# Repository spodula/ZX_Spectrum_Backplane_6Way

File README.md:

# ZX_Spectrum_Backplane_6Way
zx Spectrum backplane - 6 way

Same as the 4 way backplane except... 6 way
Also added reset button and Power LED, because why not :)
Also corrected the distances so they are all 20mm. (Seems i messed this up on the 4 way one)

Free for all use. 

Just forward the gerbers files to your favorate PCB manafactury.

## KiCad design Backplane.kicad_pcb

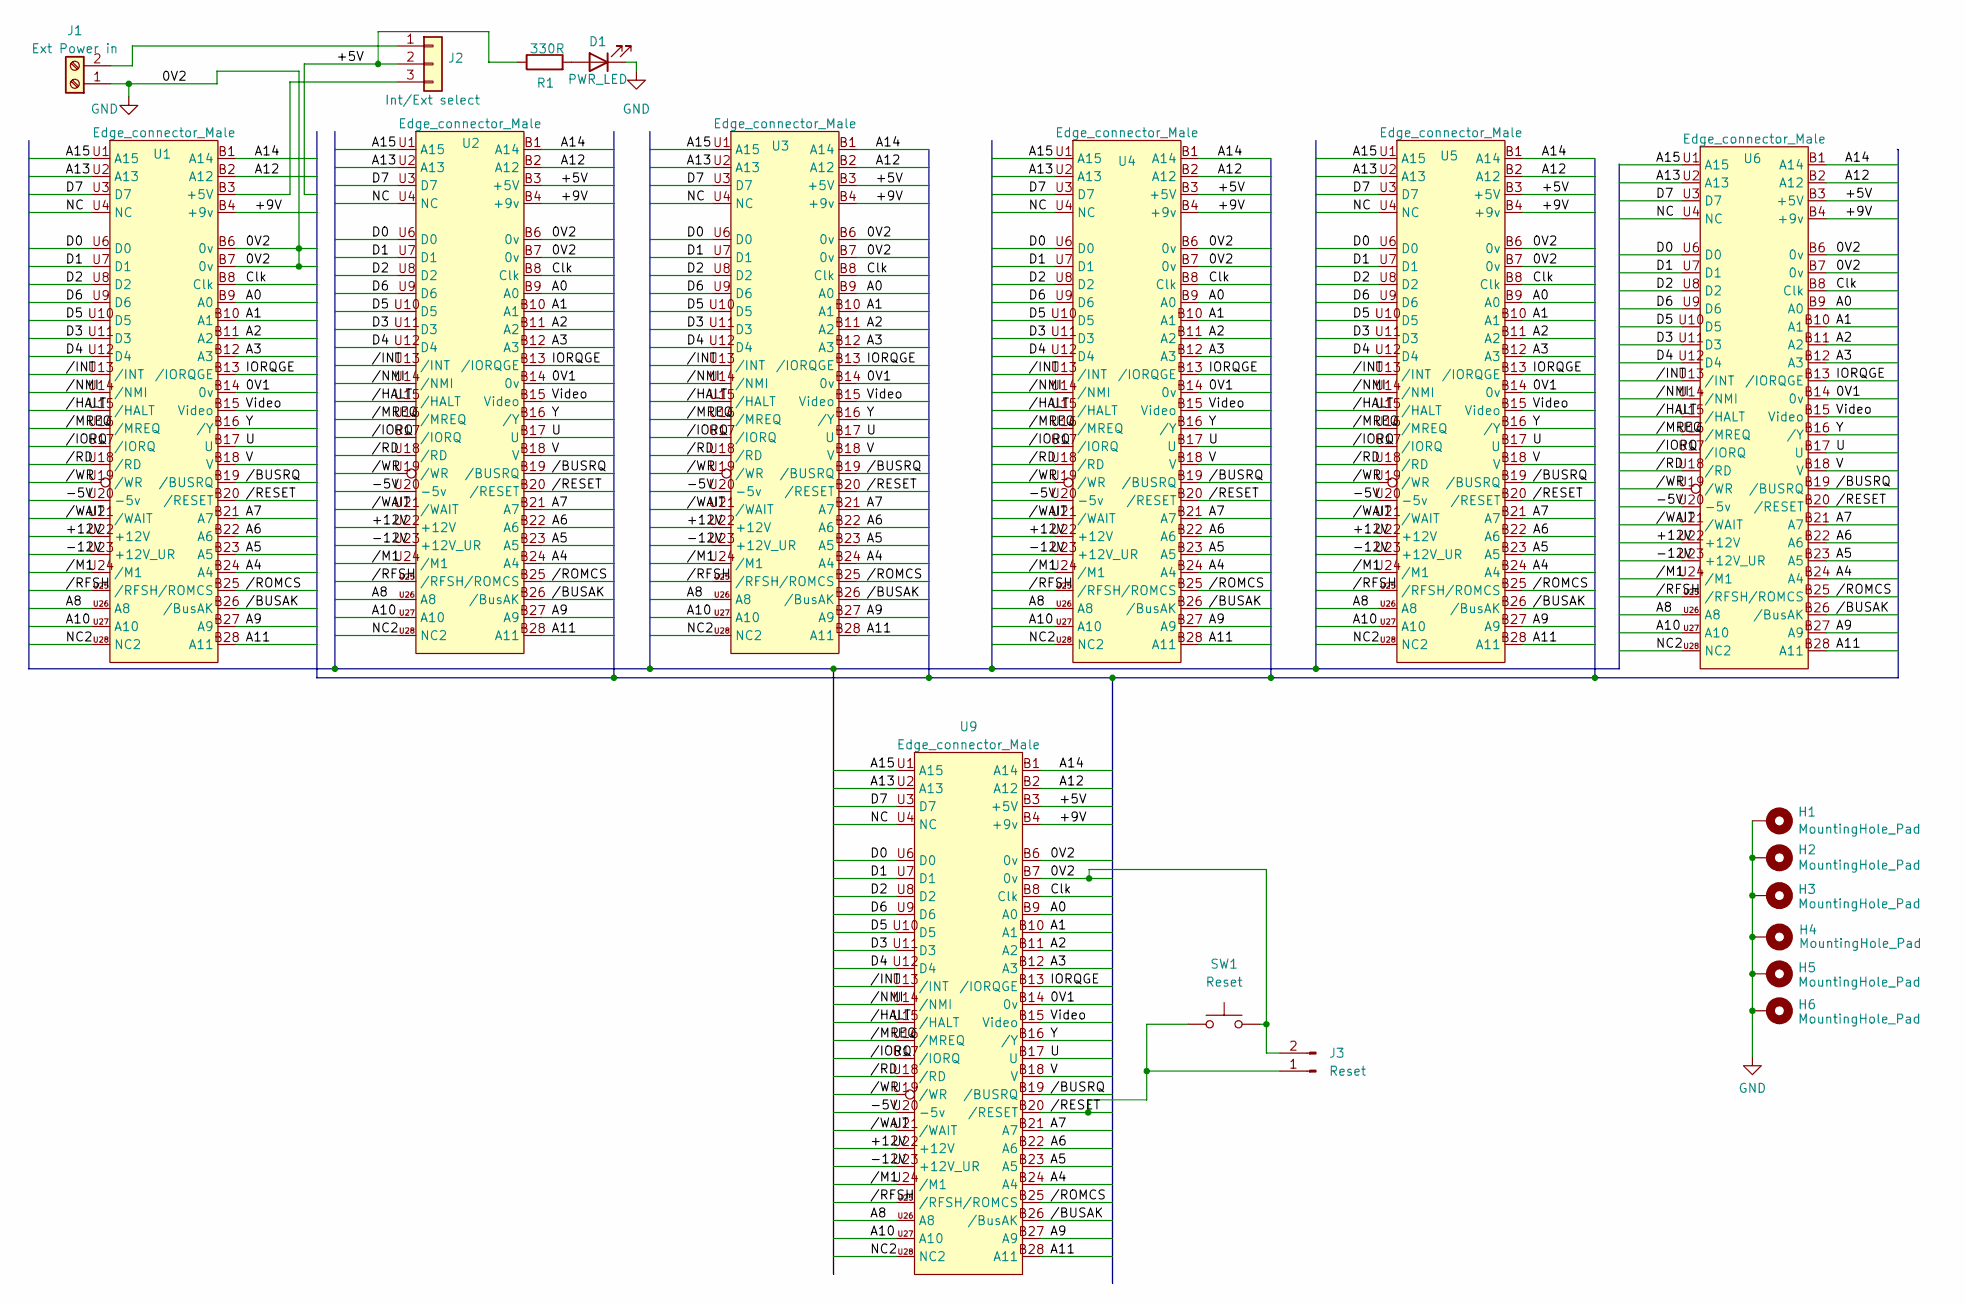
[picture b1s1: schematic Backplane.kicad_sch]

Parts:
D1: PWR_LED; LED_D5.0mm
H1, H2, H3, H4, H5, H6: MountingHole_Pad; MountingHole_2.5mm_Pad
J1: Ext Power in; TerminalBlock_bornier-2_P5.08mm
J2: Int/Ext select; PinSocket_1x03_P2.54mm_Vertical
J3: Reset; PinHeader_1x02_P2.54mm_Vertical
R1: 330R; R_Axial_DIN0207_L6.3mm_D2.5mm_P7.62mm_Horizontal
SW1: Reset; SW_PUSH_6mm_H5mm
U1: Edge_connector_Male; Speccy_edge_External
U2, U3, U4, U5, U6, U9: Edge_connector_Male; Speccy_edge_Socket_reversed

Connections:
/0V1: U1.B14 (0v), U2.B14 (0v), U3.B14 (0v), U4.B14 (0v), U5.B14 (0v), U6.B14 (0v), U9.B14 (0v)
/+5V: J2.2, R1.1, U2.B3 (+5V), U3.B3 (+5V), U4.B3 (+5V), U5.B3 (+5V), U6.B3 (+5V), U9.B3 (+5V)
/+9V: U1.B4 (+9v), U2.B4 (+9v), U3.B4 (+9v), U4.B4 (+9v), U5.B4 (+9v), U6.B4 (+9v), U9.B4 (+9v)
/+12V: U1.U22 (+12V), U2.U22 (+12V), U3.U22 (+12V), U4.U22 (+12V), U5.U22 (+12V), U6.U22 (+12V), U9.U22 (+12V)
/-5V: U1.U20 (-5v), U2.U20 (-5v), U3.U20 (-5v), U4.U20 (-5v), U5.U20 (-5v), U6.U20 (-5v), U9.U20 (-5v)
/-12V: U1.U23 (+12V_UR), U2.U23 (+12V_UR), U3.U23 (+12V_UR), U4.U23 (+12V_UR), U5.U23 (+12V_UR), U6.U23 (+12V_UR), U9.U23 (+12V_UR)
/A0: U1.B9 (A0), U2.B9 (A0), U3.B9 (A0), U4.B9 (A0), U5.B9 (A0), U6.B9 (A0), U9.B9 (A0)
/A1: U1.B10 (A1), U2.B10 (A1), U3.B10 (A1), U4.B10 (A1), U5.B10 (A1), U6.B10 (A1), U9.B10 (A1)
/A2: U1.B11 (A2), U2.B11 (A2), U3.B11 (A2), U4.B11 (A2), U5.B11 (A2), U6.B11 (A2), U9.B11 (A2)
/A3: U1.B12 (A3), U2.B12 (A3), U3.B12 (A3), U4.B12 (A3), U5.B12 (A3), U6.B12 (A3), U9.B12 (A3)
/A4: U1.B24 (A4), U2.B24 (A4), U3.B24 (A4), U4.B24 (A4), U5.B24 (A4), U6.B24 (A4), U9.B24 (A4)
/A5: U1.B23 (A5), U2.B23 (A5), U3.B23 (A5), U4.B23 (A5), U5.B23 (A5), U6.B23 (A5), U9.B23 (A5)
/A6: U1.B22 (A6), U2.B22 (A6), U3.B22 (A6), U4.B22 (A6), U5.B22 (A6), U6.B22 (A6), U9.B22 (A6)
/A7: U1.B21 (A7), U2.B21 (A7), U3.B21 (A7), U4.B21 (A7), U5.B21 (A7), U6.B21 (A7), U9.B21 (A7)
/A8: U1.U26 (A8), U2.U26 (A8), U3.U26 (A8), U4.U26 (A8), U5.U26 (A8), U6.U26 (A8), U9.U26 (A8)
/A9: U1.B27 (A9), U2.B27 (A9), U3.B27 (A9), U4.B27 (A9), U5.B27 (A9), U6.B27 (A9), U9.B27 (A9)
/A10: U1.U27 (A10), U2.U27 (A10), U3.U27 (A10), U4.U27 (A10), U5.U27 (A10), U6.U27 (A10), U9.U27 (A10)
/A11: U1.B28 (A11), U2.B28 (A11), U3.B28 (A11), U4.B28 (A11), U5.B28 (A11), U6.B28 (A11), U9.B28 (A11)
/A12: U1.B2 (A12), U2.B2 (A12), U3.B2 (A12), U4.B2 (A12), U5.B2 (A12), U6.B2 (A12), U9.B2 (A12)
/A13: U1.U2 (A13), U2.U2 (A13), U3.U2 (A13), U4.U2 (A13), U5.U2 (A13), U6.U2 (A13), U9.U2 (A13)
/A14: U1.B1 (A14), U2.B1 (A14), U3.B1 (A14), U4.B1 (A14), U5.B1 (A14), U6.B1 (A14), U9.B1 (A14)
/A15: U1.U1 (A15), U2.U1 (A15), U3.U1 (A15), U4.U1 (A15), U5.U1 (A15), U6.U1 (A15), U9.U1 (A15)
/Clk: U1.B8 (Clk), U2.B8 (Clk), U3.B8 (Clk), U4.B8 (Clk), U5.B8 (Clk), U6.B8 (Clk), U9.B8 (Clk)
/D0: U1.U6 (D0), U2.U6 (D0), U3.U6 (D0), U4.U6 (D0), U5.U6 (D0), U6.U6 (D0), U9.U6 (D0)
/D1: U1.U7 (D1), U2.U7 (D1), U3.U7 (D1), U4.U7 (D1), U5.U7 (D1), U6.U7 (D1), U9.U7 (D1)
/D2: U1.U8 (D2), U2.U8 (D2), U3.U8 (D2), U4.U8 (D2), U5.U8 (D2), U6.U8 (D2), U9.U8 (D2)
/D3: U1.U11 (D3), U2.U11 (D3), U3.U11 (D3), U4.U11 (D3), U5.U11 (D3), U6.U11 (D3), U9.U11 (D3)
/D4: U1.U12 (D4), U2.U12 (D4), U3.U12 (D4), U4.U12 (D4), U5.U12 (D4), U6.U12 (D4), U9.U12 (D4)
/D5: U1.U10 (D5), U2.U10 (D5), U3.U10 (D5), U4.U10 (D5), U5.U10 (D5), U6.U10 (D5), U9.U10 (D5)
/D6: U1.U9 (D6), U2.U9 (D6), U3.U9 (D6), U4.U9 (D6), U5.U9 (D6), U6.U9 (D6), U9.U9 (D6)
/D7: U1.U3 (D7), U2.U3 (D7), U3.U3 (D7), U4.U3 (D7), U5.U3 (D7), U6.U3 (D7), U9.U3 (D7)
/IORQGE: U1.B13 (/IORQGE), U2.B13 (/IORQGE), U3.B13 (/IORQGE), U4.B13 (/IORQGE), U5.B13 (/IORQGE), U6.B13 (/IORQGE), U9.B13 (/IORQGE)
/NC: U1.U4 (NC), U2.U4 (NC), U3.U4 (NC), U4.U4 (NC), U5.U4 (NC), U6.U4 (NC), U9.U4 (NC)
/NC2: U1.U28 (NC2), U2.U28 (NC2), U3.U28 (NC2), U4.U28 (NC2), U5.U28 (NC2), U6.U28 (NC2), U9.U28 (NC2)
/U: U1.B17 (U), U2.B17 (U), U3.B17 (U), U4.B17 (U), U5.B17 (U), U6.B17 (U), U9.B17 (U)
/V: U1.B18 (V), U2.B18 (V), U3.B18 (V), U4.B18 (V), U5.B18 (V), U6.B18 (V), U9.B18 (V)
/Video: U1.B15 (Video), U2.B15 (Video), U3.B15 (Video), U4.B15 (Video), U5.B15 (Video), U6.B15 (Video), U9.B15 (Video)
/Y: U1.B16 (/Y), U2.B16 (/Y), U3.B16 (/Y), U4.B16 (/Y), U5.B16 (/Y), U6.B16 (/Y), U9.B16 (/Y)
//BUSAK: U1.B26 (/BusAK), U2.B26 (/BusAK), U3.B26 (/BusAK), U4.B26 (/BusAK), U5.B26 (/BusAK), U6.B26 (/BusAK), U9.B26 (/BusAK)
//BUSRQ: U1.B19 (/BUSRQ), U2.B19 (/BUSRQ), U3.B19 (/BUSRQ), U4.B19 (/BUSRQ), U5.B19 (/BUSRQ), U6.B19 (/BUSRQ), U9.B19 (/BUSRQ)
//HALT: U1.U15 (/HALT), U2.U15 (/HALT), U3.U15 (/HALT), U4.U15 (/HALT), U5.U15 (/HALT), U6.U15 (/HALT), U9.U15 (/HALT)
//INT: U1.U13 (/INT), U2.U13 (/INT), U3.U13 (/INT), U4.U13 (/INT), U5.U13 (/INT), U6.U13 (/INT), U9.U13 (/INT)
//IORQ: U1.U17 (/IORQ), U2.U17 (/IORQ), U3.U17 (/IORQ), U4.U17 (/IORQ), U5.U17 (/IORQ), U6.U17 (/IORQ), U9.U17 (/IORQ)
//M1: U1.U24 (/M1), U2.U24 (/M1), U3.U24 (/M1), U4.U24 (/M1), U5.U24 (/M1), U6.U24 (/M1), U9.U24 (/M1)
//MREQ: U1.U16 (/MREQ), U2.U16 (/MREQ), U3.U16 (/MREQ), U4.U16 (/MREQ), U5.U16 (/MREQ), U6.U16 (/MREQ), U9.U16 (/MREQ)
//NMI: U1.U14 (/NMI), U2.U14 (/NMI), U3.U14 (/NMI), U4.U14 (/NMI), U5.U14 (/NMI), U6.U14 (/NMI), U9.U14 (/NMI)
//RD: U1.U18 (/RD), U2.U18 (/RD), U3.U18 (/RD), U4.U18 (/RD), U5.U18 (/RD), U6.U18 (/RD), U9.U18 (/RD)
//RESET: J3.1, SW1.1, U1.B20 (/RESET), U2.B20 (/RESET), U3.B20 (/RESET), U4.B20 (/RESET), U5.B20 (/RESET), U6.B20 (/RESET), U9.B20 (/RESET)
//RFSH: U1.U25 (/RFSH), U2.U25 (/RFSH), U3.U25 (/RFSH), U4.U25 (/RFSH), U5.U25 (/RFSH), U6.U25 (/RFSH), U9.U25 (/RFSH)
//ROMCS: U1.B25 (/ROMCS), U2.B25 (/ROMCS), U3.B25 (/ROMCS), U4.B25 (/ROMCS), U5.B25 (/ROMCS), U6.B25 (/ROMCS), U9.B25 (/ROMCS)
//WAIT: U1.U21 (/WAIT), U2.U21 (/WAIT), U3.U21 (/WAIT), U4.U21 (/WAIT), U5.U21 (/WAIT), U6.U21 (/WAIT), U9.U21 (/WAIT)
//WR: U1.U19 (/WR), U2.U19 (/WR), U3.U19 (/WR), U4.U19 (/WR), U5.U19 (/WR), U6.U19 (/WR), U9.U19 (/WR)
GND: D1.1 (K), H1.1, H2.1, H3.1, H4.1, H5.1, H6.1, J1.1, J3.2, SW1.2, U1.B6 (0v), U1.B7 (0v), U2.B6 (0v), U2.B7 (0v), U3.B6 (0v), U3.B7 (0v), U4.B6 (0v), U4.B7 (0v), U5.B6 (0v), U5.B7 (0v), U6.B6 (0v), U6.B7 (0v), U9.B6 (0v), U9.B7 (0v)
unnamed: D1.2 (A), R1.2
unnamed: J1.2, J2.1
unnamed: J2.3, U1.B3 (+5V)

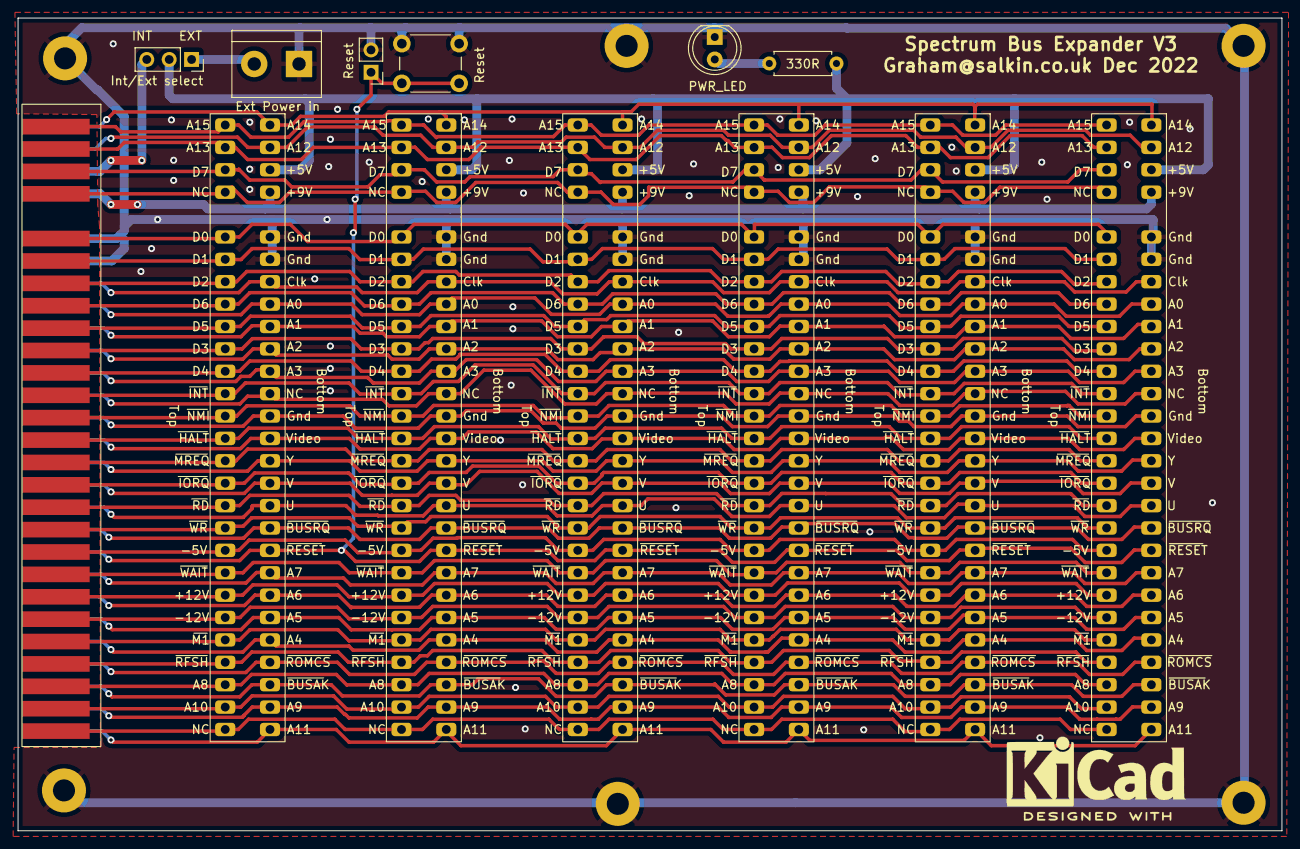
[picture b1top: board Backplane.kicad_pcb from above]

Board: 2 copper layers, 143.4 x 92.2 mm, 19 parts (0 on the bottom side), 56 nets.
